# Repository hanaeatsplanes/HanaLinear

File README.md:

# HanaLinear
> A keyboard of sorts

## What even is this??

This is an ortholinear keyboard made by yours truly :)

Features:
* Emoji Key (macOS Specific)
* Volume and Brightness Rotary Encoder
* Minimalistic Function Row

## Why does this exist??
This project was funded b

## BOM

In order to get one, you simply need to order the following components:

| Category   | Item                    |                                     | Qty | Price                   | Link                                                                    |
|------------|-------------------------|-------------------------------------|-----|-------------------------|-------------------------------------------------------------------------|
| PCB        |                         |                                     |     | $161.31                 | https://jlcpcb.com                                                      |
|            | PCB Manufacturing       |                                     | 5   | $25.90                  |                                                                         |
|            | PCBA                    |                                     | 2   |                         |                                                                         |
|            |                         | Setup Fee                           |     | $8.18                   |                                                                         |
|            |                         | Stencil                             |     | $1.53                   |                                                                         |
|            |                         | Components (14 items)               |     | $10.90                  |                                                                         |
|            |                         | SMT Asmb.                           |     | $0.97                   |                                                                         |
|            |                         | Nitrogen reflow soldering           |     | $0.85                   |                                                                         |
|            | Extended components fee |                                     |     | $9.21                   |                                                                         |
|            | Shipping                |                                     |     | $80.17                  |                                                                         |
|            | Customs                 |                                     |     | $20.15                  |                                                                         |
|            | Sales Tax               |                                     |     | $3.45                   |                                                                         |
| Components |                         |                                     |     |                         |                                                                         |
|            | Assembled by JLCPCB     |                                     |     | Included in JLCPCB Cost | https://jlcpcb.com/parts                                                |
|            |                         | 10µF 0402 capacitor                 | 4   | $0.29                   | https://jlcpcb.com/partdetail/C15525                                    |
|            |                         | 1N4148 SOD-323 diode                | 136 | $2.87                   | https://jlcpcb.com/partdetail/C437156                                   |
|            |                         | 1F 0402 capacitor                  | 4   | $0.13                   | https://jlcpcb.com/partdetail/C52923                                    |
|            |                         | 1µF 0402 capacitor                  | 4   | $0.13                   | https://jlcpcb.com/partdetail/C52923                                    |
|            |                         | 15pF 0402 capacitor                 | 4   | $0.09                   | https://jlcpcb.com/partdetail/C1548                                     |
|            |                         | 1kΩ 0402 resistor                   | 4   | $0.04                   | https://jlcpcb.com/partdetail/C11702                                    |
|            |                         | ABM8-272-T3 crystal                 | 2   | $1.46                   | https://jlcpcb.com/partdetail/C20625731                                 |
|            |                         | 100nF 0402 capacitor                | 24  | $0.36                   | https://jlcpcb.com/partdetail/C1525                                     |
|            |                         | 5.1kΩ 0402 resistor                 | 4   | $0.01                   | https://jlcpcb.com/partdetail/C25905                                    |
|            |                         | USB-C receptacle                    | 2   | $0.43                   | https://jlcpcb.com/partdetail/C2988369                                  |
|            |                         | 10kΩ 0402 resistor                  | 2   | $0.02                   | https://jlcpcb.com/partdetail/C25744                                    |
|            |                         | W25Q128JVS SOIC-8 flash memory      | 2   | $13.33                  | https://jlcpcb.com/partdetail/C97521                                    |
|            |                         | RP2040 QFN-56 microcontroller       | 2   | $4.91                   | https://jlcpcb.com/partdetail/C2040                                     |
|            |                         | AMS1117-3.3 SOT-223 voltage reg.    | 2   | $0.99                   | https://jlcpcb.com/partdetail/C6186                                     |
|            |                         | 27Ω 0603 resistor                   | 4   | $0.06                   | https://jlcpcb.com/partdetail/C25190                                    |
|            |                         | Shipping + Customs                  |     | Included in JLCPCB Cost |                                                                         |
|            | Mouser                  |                                     |     | $13.55                  | https://mouser.com                                                      |
|            |                         | PEC12R-4115F-S0012 rotary encoder   | 2   | $3.62                   | https://www.mouser.com/ProductDetail/652-PEC12R-4115F-S12               |
|            |                         | FSM2JSMAATR push button             | 2   | $0.62                   | https://www.mouser.com/ProductDetail/506-FSM2JSMAATR                    |
|            |                         | Tarrifs                             |     | $0.53                   |                                                                         |
|            |                         | Tax                                 |     | $0.29                   |                                                                         |
|            |                         | Shipping                            |     | $8.49                   |                                                                         |
|            | Keeb.io                 |                                     |     | $25.97                  | https://keeb.io                                                         |
|            |                         | Cherry MX 2u Stabilizers (6-pack)   | 1x6 | $10.99                  | https://keeb.io/products/cherry-mx-stabilizer?variant=39421968613470    |
|            |                         | Cherry MX 3u Stabilizers            | 2   | $3.98                   | https://keeb.io/products/cherry-mx-stabilizer?variant=39518829772894    |
|            |                         | Shipping                            |     | $10.10                  |                                                                         |
|            |                         | Tax                                 |     | $0.90                   |                                                                         |
|            | CannonKeys              |                                     |     | $10.44                  | https://cannonkeys.com                                                  |
|            |                         | 7u Stabilizer Wires (5-pack)        | 1x5 | $5.00                   | https://cannonkeys.com/products/stabilizer-wires?variant=32257339293807 |
|            |                         | Shipping                            |     | $5.13                   |                                                                         |
|            |                         | Tax                                 |     | $0.31                   |                                                                         |
|            | Mechanical Keyboards    |                                     |     | $36.58                  | https://mechanicalkeyboards.com/?country=US                             |
|            |                         | Cherry MX2A Black 60g Linear Switch | 70  | $28.00                  | https://mechanicalkeyboards.com/products/cherry-mx2a-black-60g-linear   |
|            |                         | Shipping                            |     | $6.90                   |                                                                         |
|            |                         | Tax                                 |     | $1.68                   |                                                                         |

## Images

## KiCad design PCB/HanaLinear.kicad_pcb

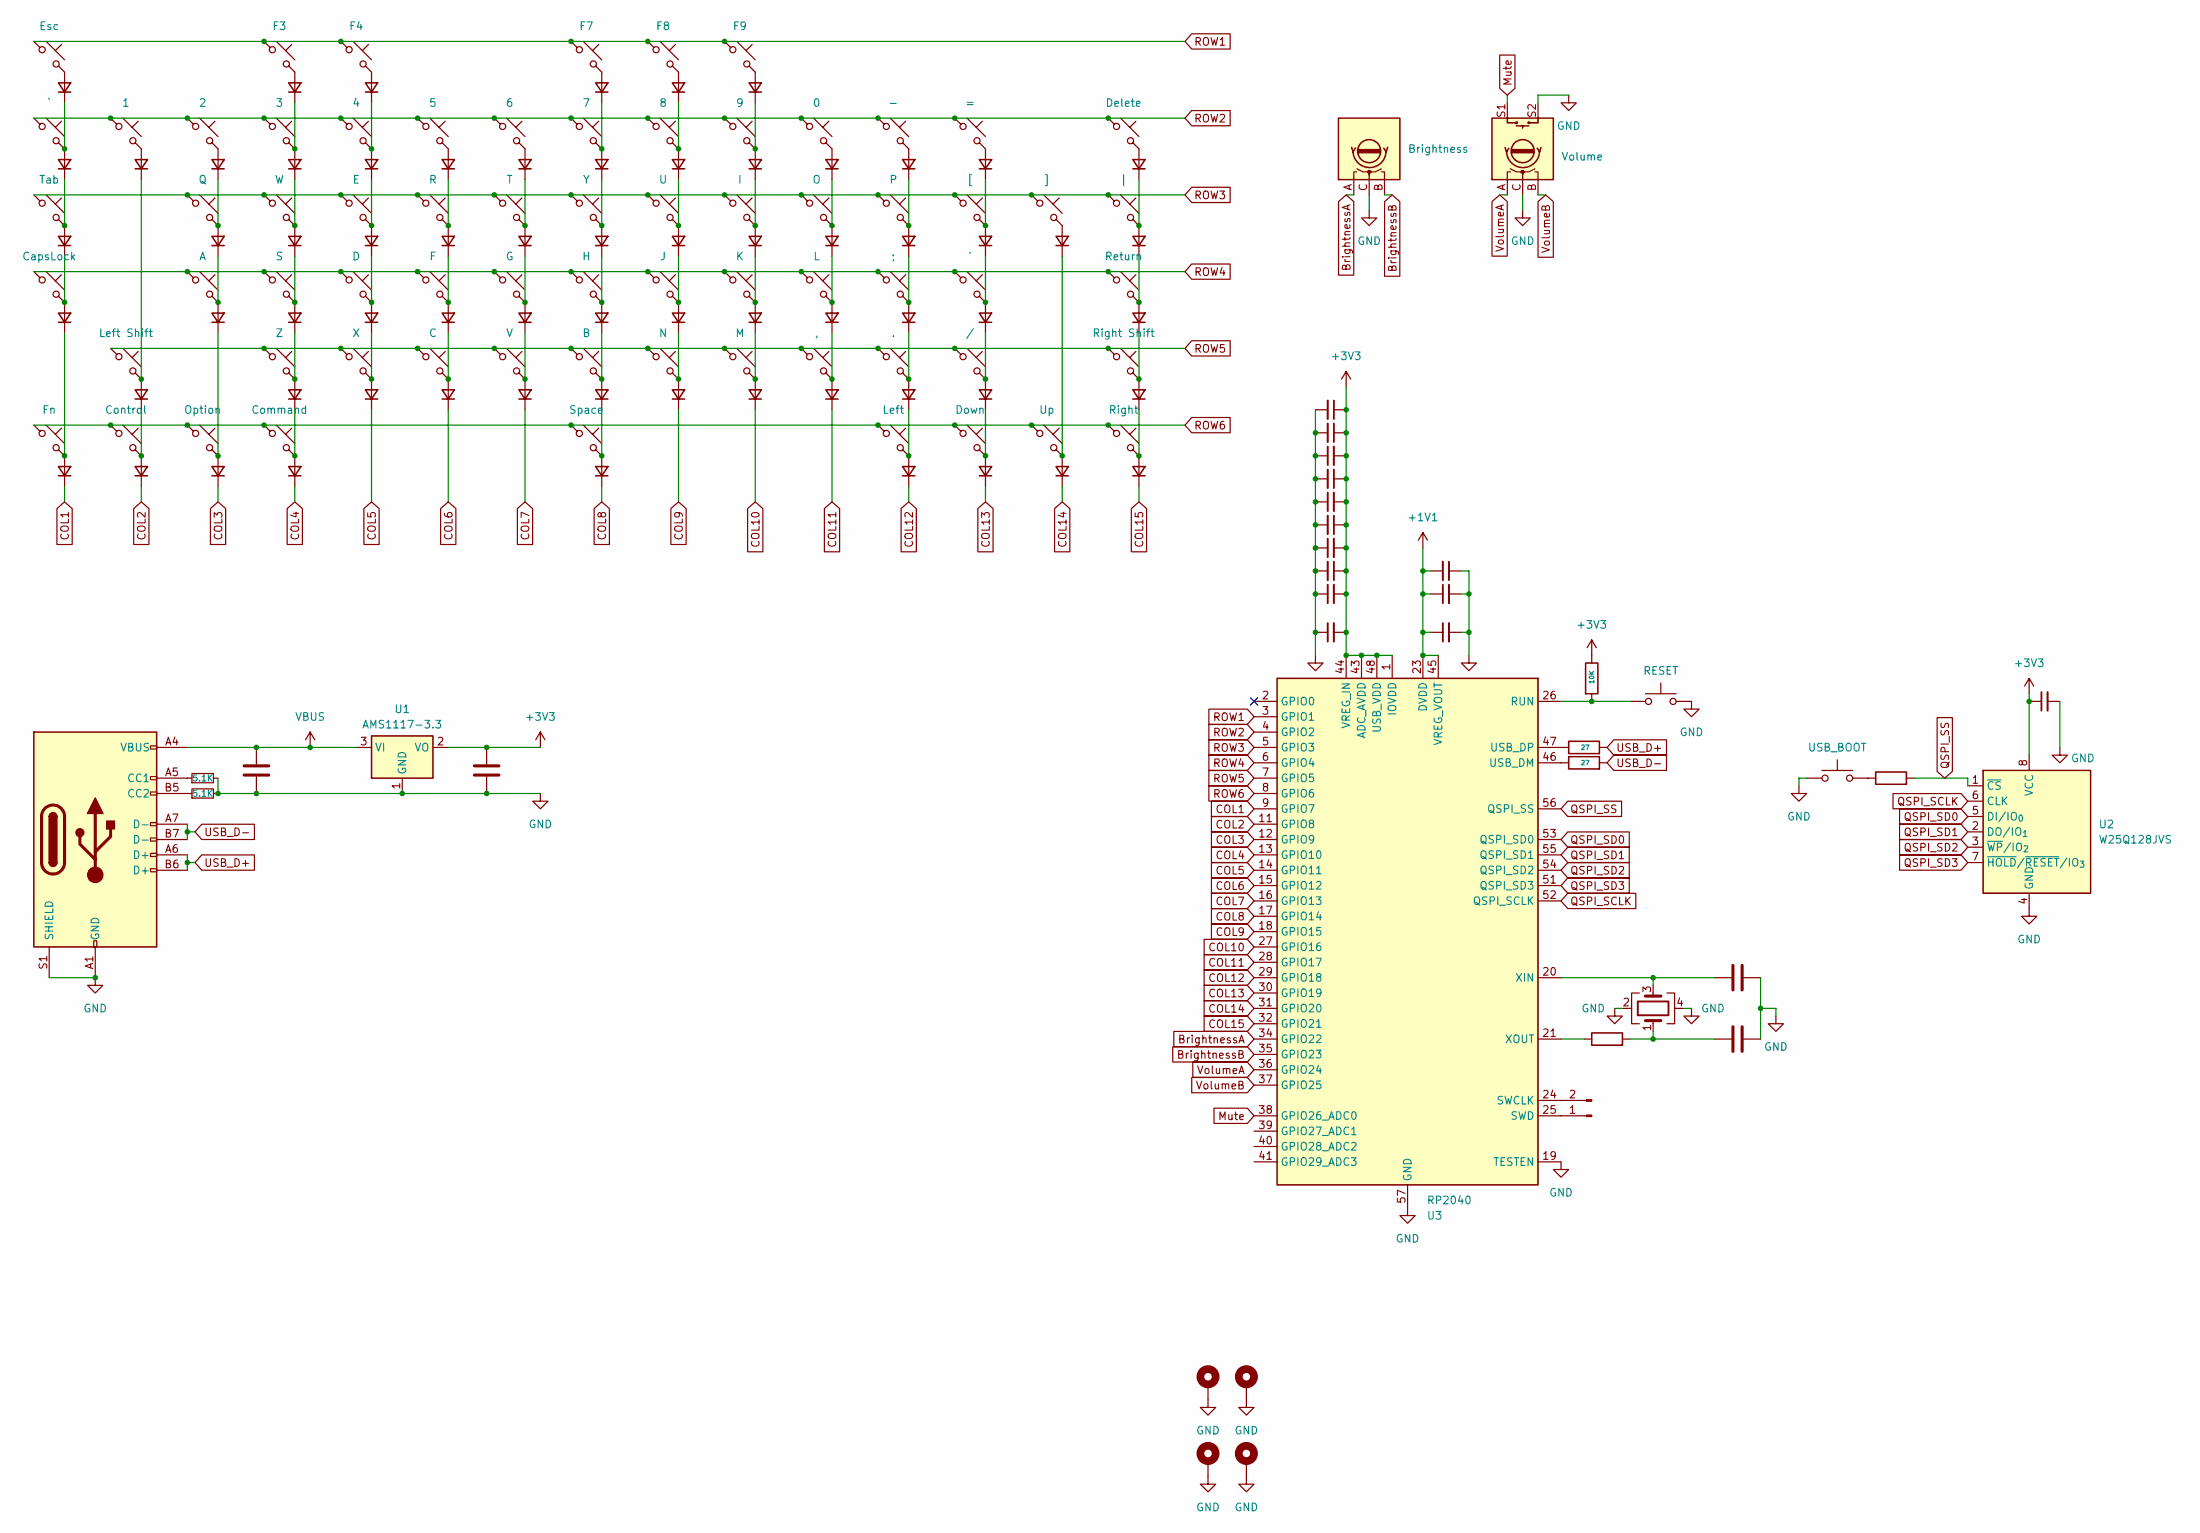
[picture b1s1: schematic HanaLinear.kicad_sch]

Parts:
C1, C2, C3, C4, C5, C6, C7, C8, C9, C10, C11, C14: 100nF; C_0402_1005Metric
C12, C13: 1uF; C_0402_1005Metric
C15, C16: 10uF; C_0402_1005Metric
C17, C20: 15pF; C_0402_1005Metric
D1, D2, D3, D4, D5, D6, D7, D8, D9, D10, D11, D12, D13, D14, D15, D16, D17, D18, D19, D20, D21, D22, D23, D24, D25, D26, D27, D28, D29, D30, D31, D32, D33, D34, D35, D36, D37, D38, D39, D40, D41, D42, D43, D44, D45, D46, D47, D48, D49, D50, D51, D52, D53, D54, D55, D56, D57, D58, D59, D60, D61, D62, D63, D64, D65, D66, D67, D68: D_Small; D_SOD-323
H1, H2, H3, H4: MountingHole_Pad; MountingHole_2.5mm_Pad_Via
J1: USB_C_Receptacle_USB2.0_14P; USB_C_Receptacle_G-Switch_GT-USB-7010ASV
J2: SW; PinSocket_1x02_P1.00mm_Vertical
R2: 10K; R_0402_1005Metric
R3, R4: 27; R_0603_1608Metric
R5, R7: 5.1K; R_0402_1005Metric
R6, R9: 1k; R_0402_1005Metric
SW1: Esc; SW_Cherry_MX_2.00u_PCB
SW2: F3; SW_Cherry_MX_1.00u_PCB
SW3: F4; SW_Cherry_MX_1.00u_PCB
SW4: F7; SW_Cherry_MX_1.00u_PCB
SW5: F8; SW_Cherry_MX_1.00u_PCB
SW6: F9; SW_Cherry_MX_1.00u_PCB
SW7: `; SW_Cherry_MX_1.00u_PCB
SW8: 1; SW_Cherry_MX_1.00u_PCB
SW9: 2; SW_Cherry_MX_1.00u_PCB
SW10: 3; SW_Cherry_MX_1.00u_PCB
SW11: 4; SW_Cherry_MX_1.00u_PCB
SW12: 5; SW_Cherry_MX_1.00u_PCB
SW13: 6; SW_Cherry_MX_1.00u_PCB
SW14: 7; SW_Cherry_MX_1.00u_PCB
SW15: 8; SW_Cherry_MX_1.00u_PCB
SW16: 9; SW_Cherry_MX_1.00u_PCB
SW17: 0; SW_Cherry_MX_1.00u_PCB
SW18: -; SW_Cherry_MX_1.00u_PCB
SW19: =; SW_Cherry_MX_1.00u_PCB
SW20: Delete; SW_Cherry_MX_2.00u_PCB
SW21: Brightness; RotaryEncoder_Bourns_Vertical_PEC12R-3x17F-Sxxxx
SW22: Volume; RotaryEncoder_Bourns_Vertical_PEC12R-3x17F-Sxxxx
SW23: Tab; SW_Cherry_MX_2.00u_PCB
SW24: Q; SW_Cherry_MX_1.00u_PCB
SW25: W; SW_Cherry_MX_1.00u_PCB
SW26: E; SW_Cherry_MX_1.00u_PCB
SW27: R; SW_Cherry_MX_1.00u_PCB
SW28: T; SW_Cherry_MX_1.00u_PCB
SW29: Y; SW_Cherry_MX_1.00u_PCB
SW30: U; SW_Cherry_MX_1.00u_PCB
SW31: I; SW_Cherry_MX_1.00u_PCB
SW32: O; SW_Cherry_MX_1.00u_PCB
SW33: P; SW_Cherry_MX_1.00u_PCB
SW34: [; SW_Cherry_MX_1.00u_PCB
SW35: ]; SW_Cherry_MX_1.00u_PCB
SW36: |; SW_Cherry_MX_1.00u_PCB
SW37: CapsLock; SW_Cherry_MX_2.00u_PCB
SW38: A; SW_Cherry_MX_1.00u_PCB
SW39: S; SW_Cherry_MX_1.00u_PCB
SW40: D; SW_Cherry_MX_1.00u_PCB
SW41: F; SW_Cherry_MX_1.00u_PCB
SW42: G; SW_Cherry_MX_1.00u_PCB
SW43: H; SW_Cherry_MX_1.00u_PCB
SW44: J; SW_Cherry_MX_1.00u_PCB
SW45: K; SW_Cherry_MX_1.00u_PCB
SW46: L; SW_Cherry_MX_1.00u_PCB
SW47: ;; SW_Cherry_MX_1.00u_PCB
SW48: '; SW_Cherry_MX_1.00u_PCB
SW49: Return; SW_Cherry_MX_2.00u_PCB
SW50: Left Shift; SW_Cherry_MX_1.00u_PCB
SW51: Z; SW_Cherry_MX_1.00u_PCB
SW52: X; SW_Cherry_MX_1.00u_PCB
SW53: C; SW_Cherry_MX_1.00u_PCB
SW54: V; SW_Cherry_MX_1.00u_PCB
SW55: B; SW_Cherry_MX_1.00u_PCB
SW56: N; SW_Cherry_MX_1.00u_PCB
SW57: M; SW_Cherry_MX_1.00u_PCB
SW58: ,; SW_Cherry_MX_1.00u_PCB
SW59: .; SW_Cherry_MX_1.00u_PCB
SW60: /; SW_Cherry_MX_1.00u_PCB
SW61: Right Shift; SW_Cherry_MX_2.00u_PCB
SW62: Fn; SW_Cherry_MX_1.00u_PCB
SW63: Control; SW_Cherry_MX_1.00u_PCB
SW64: Option; SW_Cherry_MX_1.00u_PCB
SW65: Command; SW_Cherry_MX_1.00u_PCB
SW66: Space; SW_Cherry_MX_1.00u_PCB
SW67: Left; SW_Cherry_MX_1.00u_PCB
SW68: Down; SW_Cherry_MX_1.00u_PCB
SW69: Up; SW_Cherry_MX_1.00u_PCB
SW70: Right; SW_Cherry_MX_1.00u_PCB
SW72: RESET; SW_PUSH_6mm
SW73: USB_BOOT; SW_PUSH_6mm
U1: AMS1117-3.3; SOT-223-3_TabPin2
U2: W25Q128JVS; SOIC-8_5.3x5.3mm_P1.27mm
U3: RP2040; QFN-56-1EP_7x7mm_P0.4mm_EP3.2x3.2mm
Y1: ABM8-272-T3; Crystal_SMD_3225-4Pin_3.2x2.5mm

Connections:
+1V1: C9.2, C11.1, C13.1, U3.23 (DVDD), U3.45 (VREG_VOUT), U3.50 (DVDD)
+3V3: C1.1, C2.1, C3.2, C4.1, C5.2, C6.1, C7.2, C8.1, C10.2, C12.2, C14.1, C16.1, R2.1, U1.2 (VO), U2.8 (VCC), U3.1 (IOVDD), U3.10 (IOVDD), U3.22 (IOVDD), U3.33 (IOVDD), U3.42 (IOVDD), U3.43 (ADC_AVDD), U3.44 (VREG_IN), U3.48 (USB_VDD), U3.49 (IOVDD)
BrightnessA: SW21.A, U3.34 (GPIO22)
BrightnessB: SW21.B, U3.35 (GPIO23)
COL1: D60.1 (K), U3.9 (GPIO7)
COL2: D61.1 (K), U3.11 (GPIO8)
COL3: D62.1 (K), U3.12 (GPIO9)
COL4: D63.1 (K), U3.13 (GPIO10)
COL5: D50.1 (K), U3.14 (GPIO11)
COL6: D51.1 (K), U3.15 (GPIO12)
COL7: D52.1 (K), U3.16 (GPIO13)
COL8: D64.1 (K), U3.17 (GPIO14)
COL9: D54.1 (K), U3.18 (GPIO15)
COL10: D55.1 (K), U3.27 (GPIO16)
COL11: D56.1 (K), U3.28 (GPIO17)
COL12: D65.1 (K), U3.29 (GPIO18)
COL13: D66.1 (K), U3.30 (GPIO19)
COL14: D67.1 (K), U3.31 (GPIO20)
COL15: D68.1 (K), U3.32 (GPIO21)
GND: C1.2, C2.2, C3.1, C4.2, C5.1, C6.2, C7.1, C8.2, C9.1, C10.1, C11.2, C12.1, C13.2, C14.2, C15.2, C16.2, C17.2, C20.2, H1.1, H2.1, H3.1, H4.1, J1.A1 (GND), J1.A12 (GND), J1.B1 (GND), J1.B12 (GND), J1.S1 (SHIELD), R5.2, R7.2, SW21.C, SW22.C, SW22.S2, SW72.1, SW73.1, U1.1 (GND), U2.4 (GND), U3.19 (TESTEN), U3.57 (GND), Y1.2, Y1.4
Mute: SW22.S1, U3.38 (GPIO26_ADC0)
unnamed: C20.1, R9.2, Y1.1
unnamed: D1.2 (A), SW1.2
unnamed: D1.1 (K), D7.2 (A), SW7.2
unnamed: D2.2 (A), SW2.2
unnamed: D3.2 (A), SW3.2
unnamed: D4.2 (A), SW4.2
unnamed: D5.2 (A), SW5.2
unnamed: D6.2 (A), SW6.2
unnamed: D8.2 (A), SW8.2
unnamed: D9.2 (A), SW9.2
unnamed: D2.1 (K), D10.2 (A), SW10.2
unnamed: D10.1 (K), D23.2 (A), SW25.2
unnamed: D3.1 (K), D11.2 (A), SW11.2
unnamed: D11.1 (K), D24.2 (A), SW26.2
unnamed: D12.2 (A), SW12.2
unnamed: D12.1 (K), D25.2 (A), SW27.2
unnamed: D13.2 (A), SW13.2
unnamed: D13.1 (K), D26.2 (A), SW28.2
unnamed: D4.1 (K), D14.2 (A), SW14.2
unnamed: D14.1 (K), D27.2 (A), SW29.2
unnamed: D5.1 (K), D15.2 (A), SW15.2
unnamed: D15.1 (K), D28.2 (A), SW30.2
unnamed: D6.1 (K), D16.2 (A), SW16.2
unnamed: D16.1 (K), D29.2 (A), SW31.2
unnamed: D17.2 (A), SW17.2
unnamed: D17.1 (K), D30.2 (A), SW32.2
unnamed: D18.2 (A), SW18.2
unnamed: D18.1 (K), D31.2 (A), SW33.2
unnamed: D19.2 (A), SW19.2
unnamed: D19.1 (K), D32.2 (A), SW34.2
unnamed: D20.2 (A), SW20.2
unnamed: D20.1 (K), D34.2 (A), SW36.2
unnamed: D7.1 (K), D21.2 (A), SW23.2
unnamed: D21.1 (K), D35.2 (A), SW37.2
unnamed: D9.1 (K), D22.2 (A), SW24.2
unnamed: D22.1 (K), D36.2 (A), SW38.2
unnamed: D23.1 (K), D37.2 (A), SW39.2
unnamed: D24.1 (K), D38.2 (A), SW40.2
unnamed: D25.1 (K), D39.2 (A), SW41.2
unnamed: D26.1 (K), D40.2 (A), SW42.2
unnamed: D27.1 (K), D41.2 (A), SW43.2
unnamed: D28.1 (K), D42.2 (A), SW44.2
unnamed: D29.1 (K), D43.2 (A), SW45.2
unnamed: D30.1 (K), D44.2 (A), SW46.2
unnamed: D31.1 (K), D45.2 (A), SW47.2
unnamed: D32.1 (K), D46.2 (A), SW48.2
unnamed: D33.2 (A), SW35.2
unnamed: D33.1 (K), D67.2 (A), SW69.2
unnamed: D34.1 (K), D47.2 (A), SW49.2
unnamed: D35.1 (K), D60.2 (A), SW62.2
unnamed: D36.1 (K), D62.2 (A), SW64.2
unnamed: D37.1 (K), D49.2 (A), SW51.2
unnamed: D38.1 (K), D50.2 (A), SW52.2
unnamed: D39.1 (K), D51.2 (A), SW53.2
unnamed: D40.1 (K), D52.2 (A), SW54.2
unnamed: D41.1 (K), D53.2 (A), SW55.2
unnamed: D42.1 (K), D54.2 (A), SW56.2
unnamed: D43.1 (K), D55.2 (A), SW57.2
unnamed: D44.1 (K), D56.2 (A), SW58.2
unnamed: D45.1 (K), D57.2 (A), SW59.2
unnamed: D46.1 (K), D58.2 (A), SW60.2
unnamed: D47.1 (K), D59.2 (A), SW61.2
unnamed: D8.1 (K), D48.2 (A), SW50.2
unnamed: D48.1 (K), D61.2 (A), SW63.2
unnamed: D49.1 (K), D63.2 (A), SW65.2
unnamed: D53.1 (K), D64.2 (A), SW66.2
unnamed: D57.1 (K), D65.2 (A), SW67.2
unnamed: D58.1 (K), D66.2 (A), SW68.2
unnamed: D59.1 (K), D68.2 (A), SW70.2
unnamed: J1.A5 (CC1), R5.1
unnamed: J1.B5 (CC2), R7.1
unnamed: J2.1, U3.25 (SWD)
unnamed: J2.2, U3.24 (SWCLK)
unnamed: R6.1, SW73.2
unnamed: R2.2, SW72.2, U3.26 (RUN)
unnamed: R4.1, U3.46 (USB_DM)
unnamed: R3.1, U3.47 (USB_DP)
unnamed: C17.1, U3.20 (XIN), Y1.3
unnamed: R9.1, U3.21 (XOUT)
QSPI_SCLK: U2.6 (CLK), U3.52 (QSPI_SCLK)
QSPI_SD0: U2.5 (DI/IO_{0}), U3.53 (QSPI_SD0)
QSPI_SD1: U2.2 (DO/IO_{1}), U3.55 (QSPI_SD1)
QSPI_SD2: U2.3 (~WP/IO_{2}), U3.54 (QSPI_SD2)
QSPI_SD3: U2.7 (~HOLD/~RESET/IO_{3}), U3.51 (QSPI_SD3)
QSPI_SS: R6.2, U2.1 (~CS), U3.56 (QSPI_SS)
ROW1: SW1.1, SW2.1, SW3.1, SW4.1, SW5.1, SW6.1, U3.3 (GPIO1)
ROW2: SW7.1, SW8.1, SW9.1, SW10.1, SW11.1, SW12.1, SW13.1, SW14.1, SW15.1, SW16.1, SW17.1, SW18.1, SW19.1, SW20.1, U3.4 (GPIO2)
ROW3: SW23.1, SW24.1, SW25.1, SW26.1, SW27.1, SW28.1, SW29.1, SW30.1, SW31.1, SW32.1, SW33.1, SW34.1, SW35.1, SW36.1, U3.5 (GPIO3)
ROW4: SW37.1, SW38.1, SW39.1, SW40.1, SW41.1, SW42.1, SW43.1, SW44.1, SW45.1, SW46.1, SW47.1, SW48.1, SW49.1, U3.6 (GPIO4)
ROW5: SW50.1, SW51.1, SW52.1, SW53.1, SW54.1, SW55.1, SW56.1, SW57.1, SW58.1, SW59.1, SW60.1, SW61.1, U3.7 (GPIO5)
ROW6: SW62.1, SW63.1, SW64.1, SW65.1, SW66.1, SW67.1, SW68.1, SW69.1, SW70.1, U3.8 (GPIO6)
USB_D+: J1.A6 (D+), J1.B6 (D+), R3.2
USB_D-: J1.A7 (D-), J1.B7 (D-), R4.2
VBUS: C15.1, J1.A4 (VBUS), J1.A9 (VBUS), J1.B4 (VBUS), J1.B9 (VBUS), U1.3 (VI)
VolumeA: SW22.A, U3.36 (GPIO24)
VolumeB: SW22.B, U3.37 (GPIO25)

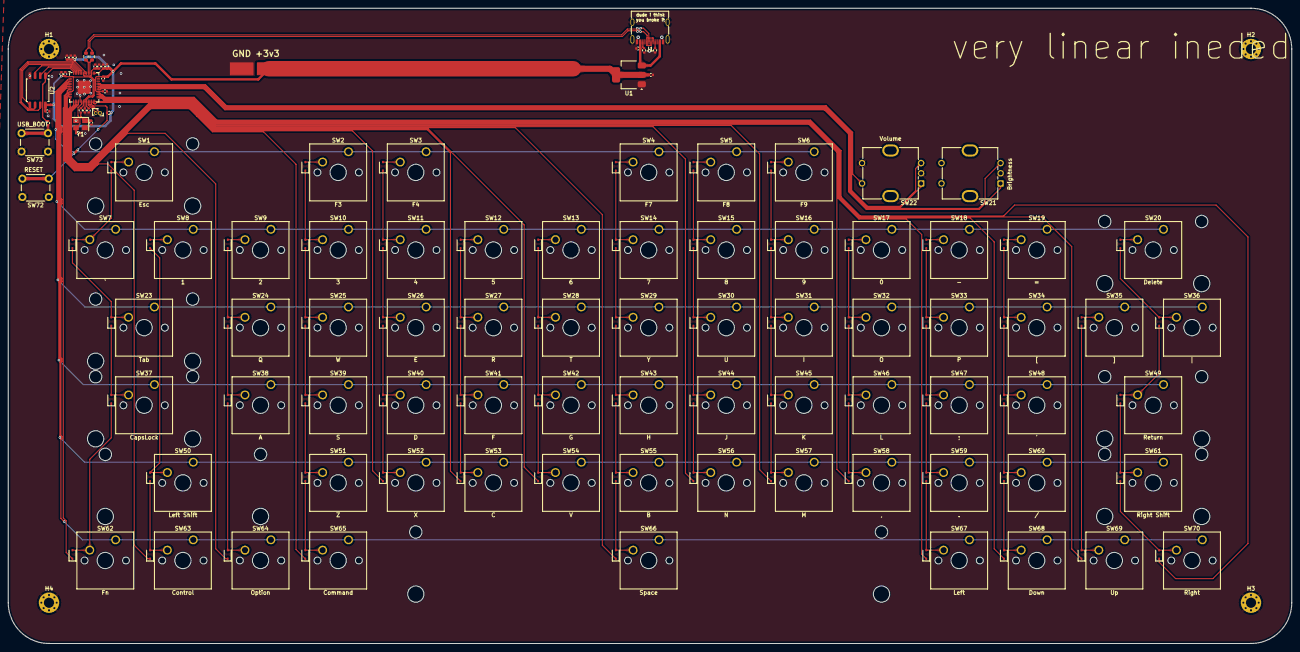
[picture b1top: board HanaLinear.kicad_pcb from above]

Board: 2 copper layers, 315.0 x 155.9 mm, 175 parts (0 on the bottom side), 117 nets.

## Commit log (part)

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2026-06-13 init
2026-06-13 Update JOURNAL.md with session notes
    Added notes about keyboard layout and session observations.
2026-06-13 add layout
2026-06-13 Update JOURNAL.md with keyboard layout reflections
    Added images and personal thoughts about a keyboard layout.
2026-06-13 Update JOURNAL.md with image and notes
    Added an image and updated the post session write-up.
2026-06-13 Update JOURNAL.md with total time and session info
    Added total time and updated session details.
2026-06-13 Fix time format and add new session entries
    Updated time format and added new session details.
2026-06-13 Update JOURNAL.md with session notes and image
    Added a during session write-up section with an image and notes.
2026-06-14 Edit JOURNAL.md with time entries and reflections
    Updated time tracking and added post-session reflections for Day 1 and Day 2.
2026-06-14 add row/col labels
2026-06-14 Update JOURNAL.md with session notes
    Added notes about wiring and component choices during the session.
2026-06-15 Update JOURNAL.md with Day 2 and Day 3 entries
    Added end time and time spent working for Day 2. Started Day 3 with initial notes on rotary encoders.
2026-06-15 Update JOURNAL.md with new entries
    Added thoughts on rotary encoders and USB 3.0 challenges.
2026-06-15 OH MY GOD
2026-06-15 fix layout
2026-06-15 you and me sunday drifvin
2026-06-15 Update JOURNAL.md with images and reflections
    Added images and expressed excitement about finishing a task.
2026-06-15 Update JOURNAL.md with recent stabilizer notes
2026-06-15 Update JOURNAL.md with part selection details
    Added images and notes about part selection process.
2026-06-15 Update JOURNAL.md with part selection notes
    Added images and notes about part selection for PCB.
2026-06-15 Add images and update journal entry
2026-06-15 Update JOURNAL.md with images and comments
    Added two images and a comment about finishing the PCB.
2026-06-15 Update JOURNAL.md with new images and content
    Added additional images and text to the journal.
2026-06-15 Add end time and time spent for Day 3
    Updated journal entry for Day 3 with end time and time spent working.
2026-06-16 Document Day 4 progress in JOURNAL.md
    Added updates for Day 4 of the project, including progress on wiring and JLCPCB rules.
2026-06-16 Update JOURNAL.md with recent project progress
    Added JLCPCB rules and documented wiring progress for RP2040.
2026-06-16 Update JOURNAL.md with session information
    Added session details and image reference to JOURNAL.md.
2026-06-16 Update total time from 1h to 14 hours
2026-06-16 Update JOURNAL.md with session notes and to-do list
    Added a to-do list and additional notes for the session.
2026-06-16 Update JOURNAL.md with session notes and image
2026-06-16 Update JOURNAL.md with new images and notes
    Added images and updated text regarding USB wiring and rotary encoders.
2026-06-16 glnsalfjnds,f
2026-06-16 Add images and text to JOURNAL.md
2026-06-16 Update total time and session entries in JOURNAL.md
    Updated total time and added session details.
2026-06-17 fahh
2026-06-17 Update JOURNAL.md with session details
    Added session timing and image to journal entry.
2026-06-17 sdklafjslkdfj
2026-06-17 Update JOURNAL.md with images and commentary
    Added images and commentary about transitioning from PCB design to firmware.
2026-06-17 Update JOURNAL.md with firmware transition notes
    Added reflections on transitioning from PCB design to firmware development.
2026-06-17 ghit'
2026-06-17 fasjdka
2026-06-17 Revise total time and session entries in JOURNAL.md
    Updated total time and session details in the journal.
2026-06-17 gdskfakldf
2026-06-17 oops
2026-06-25 Add Day 4 entry to JOURNAL.md
    Added entry for Day 4 with session details.
2026-06-25 Add notes for pre and during session
2026-06-25 adsfjdlfka
2026-06-26 update footprint
2026-06-27 afdklsjdfkl
2026-06-27 asdfjlkz
2026-06-27 Revise JOURNAL.md with part updates and images
    Updated journal entry with new part information and image.
2026-06-27 Revise journal entries for June 26th and 27th
    Updated Day 5 and added Day 6 entries with session details.
2026-06-28 dskjalfjlkf
2026-06-28 I SWEAR ILL CAD
2026-06-29 Update JOURNAL.md with new session entries
2026-06-29 Update JOURNAL.md with PCB project notes
    Documented progress on PCB design and rewiring tasks.
2026-06-29 dlfksaljfkj
2026-06-29 pcb adkosjfc
2026-06-30 Update JOURNAL.md with session notes and image
    Added an image and updated notes about the session.
2026-06-30 sdfkajlkf
2026-06-30 Add journal entry for day 9
    Added entry for day 9 of the journal including start time, end time, and session notes.
2026-06-30 Update JOURNAL.md with shopping details and image
    Added an image and updated shopping notes in JOURNAL.md.
